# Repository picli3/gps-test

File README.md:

# gps-test

Plataforma de pruebas para GPS con **ESP32**, pantalla OLED, cargador, step-up y bloques auxiliares de interfaz.

## Propósito del proyecto
Este diseño parece orientado a validar o construir un equipo portátil de posicionamiento/visualización, integrando alimentación, procesamiento y despliegue de datos dentro de una sola solución modular.

## Qué incluye
- esquemáticos por bloques: GPS, ESP32, OLED, cargador, step-up y auxiliares
- PCB principal en KiCad
- base útil para experimentación con localización y dispositivos portátiles

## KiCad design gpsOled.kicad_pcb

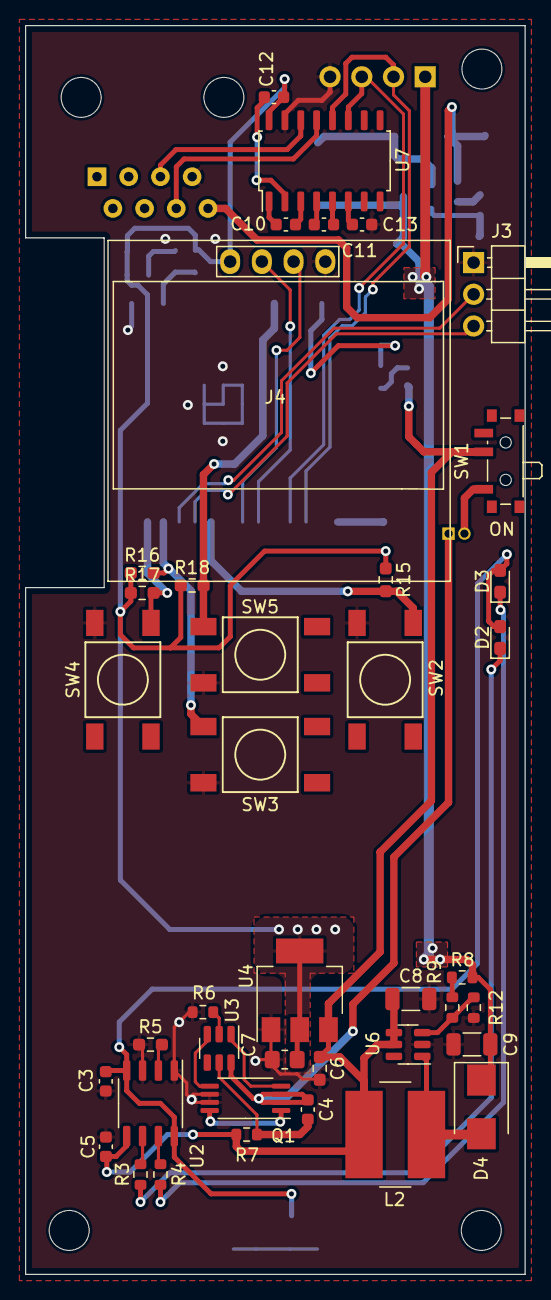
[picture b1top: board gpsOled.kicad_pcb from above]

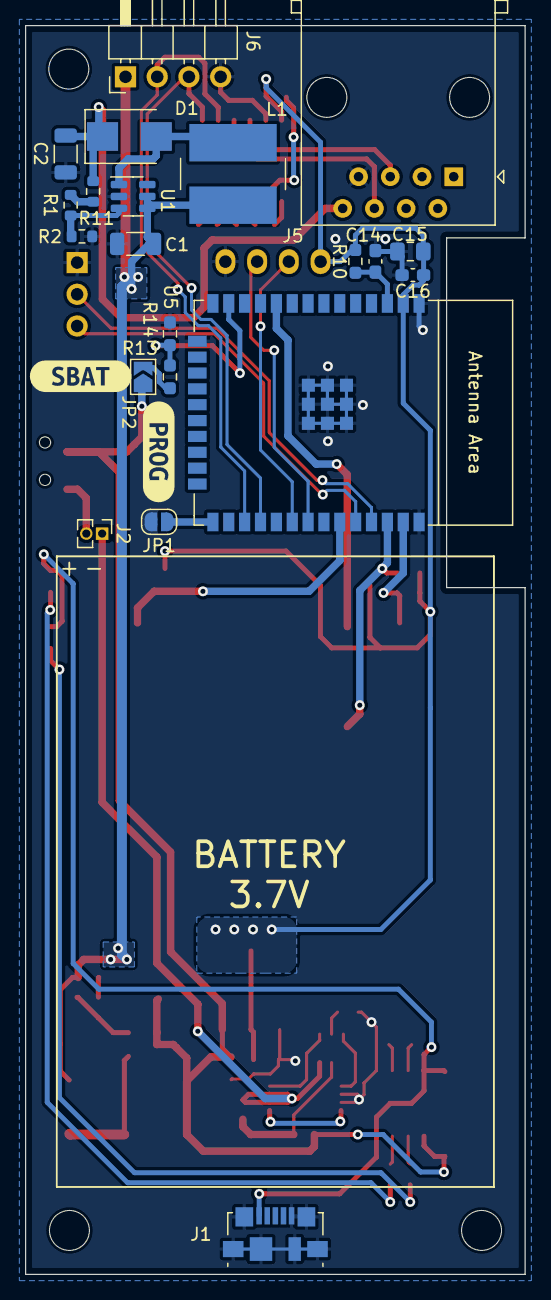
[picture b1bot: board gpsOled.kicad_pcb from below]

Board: 2 copper layers, 40.0 x 100.0 mm, 66 parts (23 on the bottom side), 46 nets.

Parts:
C1, C2, C8, C9: 22uF; C_1206_3216Metric
C3, C4: 0.1uF; C_0603_1608Metric
C5: 10uF; C_0603_1608Metric
C6: 0.1uF; R_0603_1608Metric_Pad0.98x0.95mm_HandSolder
C7: 10uF; R_0805_2012Metric_Pad1.20x1.40mm_HandSolder
C10: C; C_0603_1608Metric
C11, C12, C13: C_0603_1608Metric
C14, C16: 100nF; C_0603_1608Metric_Pad1.08x0.95mm_HandSolder
C15: 22uF; C_0805_2012Metric_Pad1.18x1.45mm_HandSolder
D1, D4: SS34; D_SMB
D2: B; LED_0603_1608Metric_Pad1.05x0.95mm_HandSolder
D3: R; LED_0603_1608Metric_Pad1.05x0.95mm_HandSolder
H1, H2: MountingHole; MountingHole_3.2mm_M3_DIN965
H3: MountingHole; MountingHole_3.2mm_M3
J1: USB_B_Micro; USB_Micro-B_Molex_47346-0001
J2: Conn_01x02; PinHeader_1x02_P1.27mm_Vertical
J3: Conn_01x03; PinHeader_1x03_P2.54mm_Horizontal
J4: SSD1306; 128x64OLED
J5: RJ45; RJ45_GEN_ZQP_Horizontal
J6: Conn_01x04; PinHeader_1x04_P2.54mm_Horizontal
JP1: Jumper_2_Open; SolderJumper-2_P1.3mm_Open_RoundedPad1.0x1.5mm
JP2: Jumper_2_Open; SolderJumper-2_P1.3mm_Open_TrianglePad1.0x1.5mm
L1, L2: 22uH; L_Bourns-SDE0805A_7x7.8mm
Q1: FS8205A; TSSOP-8_4.4x3mm_P0.65mm
R1: 22K; R_0603_1608Metric
R2, R12: 2.2k; R_0603_1608Metric
R3, R4, R6: 1k; R_0603_1608Metric
R5: 1.2k; R_0603_1608Metric_Pad0.98x0.95mm_HandSolder
R7: 100; R_0603_1608Metric
R8: 10K; R_0603_1608Metric
R9: 6.2K; R_0603_1608Metric
R10, R13, R14, R15, R16, R17, R18: 10k; R_0603_1608Metric_Pad0.98x0.95mm_HandSolder
R11: 20K; R_0603_1608Metric
SW1: on/off; SW_SPDT_PCM12
SW2, SW3, SW5: TL3301AF160QG
SW4: SW_Push; TL3301AF160QG
U1, U6: SDB628; SOT-23-6
U2: TP4056; SOP-8_3.9x4.9mm_P1.27mm
U3: DW01A; SOT-23-6
U4: AP1117-33; SOT-223-3_TabPin2
U5: ESP32-WROOM-E; ESP32-WROOM-32E
U7: MAX3232; SOIC-16_4.55x10.3mm_P1.27mm
kibuzzard-627F1822: G***; kibuzzard-627F1822
kibuzzard-629C15DA: G***; kibuzzard-629C15DA

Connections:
+3V3: C7.1, C12.1, C15.1, C16.1, J4.1, R10.1, R15.1, R16.1, R17.1, R18.1, U4.2 (VO), U5.2 (3V3), U7.16 (VCC)
+5V: C1.1, C9.1, D4.1 (K), J6.1, L1.1, R8.1, U1.4 (EN), U1.5 (IN)
+12V: C2.1, D1.1 (K), J5.8, R11.1
/ESP32/RST: C14.1, R10.2, U5.3 (EN/CHIP_PU)
/ESP32/SCL: J4.3, U5.31 (GPIO19)
/ESP32/SDA: J4.2, U5.30 (GPIO18)
/ESP32/UART_RX_0: J3.3, U5.34 (U0RXD/GPIO3)
/ESP32/UART_RX_2: J6.2, U5.27 (GPIO16), U7.12 (R1OUT)
/ESP32/UART_TX_0: J3.2, U5.35 (U0TXD/GPIO1)
/ESP32/UART_TX_2: J6.3, U5.28 (GPIO17), U7.11 (T1IN)
/RS232/RS232_TX: J5.5, U7.14 (T1OUT)
/RS232/RS323_RX: J5.6, U7.13 (R1IN)
/batt_status: JP2.2 (B), R13.1
/charger/BAT+: J2.2, SW1.1 (A)
/charger/BAT-: C4.2, J2.1, Q1.2 (D), Q1.3 (D), U3.6 (GND)
/charger/STEP-UP2/VIN: C5.1, C6.1, C8.1, JP2.1 (A), L2.1, R7.2, SW1.2 (B), U2.5 (BAT), U4.3 (VI), U6.4 (EN), U6.5 (IN)
/charger/VBUS: C3.1, D2.2 (A), D3.2 (A), J1.1 (VBUS), U2.4 (VCC), U2.8 (CE)
GND: C1.2, C2.2, C3.2, C5.2, C6.2, C7.2, C8.2, C9.2, C13.1, C14.2, C15.2, C16.2, J1.5 (GND), J1.6 (Shield), J3.1, J4.4, J5.7, J6.4, JP1.1 (A), Q1.6 (S), Q1.7 (S), R2.2, R5.1, R6.2, R12.2, R14.2, SW2.2, SW3.2, SW4.2, SW5.2, U1.2 (GND), U2.1 (TEMP), U2.3 (GND), U4.1 (GND), U5.1 (GND), U5.15 (GND), U5.38 (GND), U5.39 (GND_THERMAL), U6.2 (GND), U7.15 (GND)
unnamed: C4.1, R7.1, U3.5 (VCC)
unnamed: C10.1, U7.1 (C1+)
unnamed: C10.2, U7.3 (C1-)
unnamed: C11.1, U7.4 (C2+)
unnamed: C11.2, U7.5 (C2-)
unnamed: C12.2, U7.2 (VS+)
unnamed: C13.2, U7.6 (VS-)
unnamed: D1.2 (A), L1.2, U1.1 (SW)
unnamed: D2.1 (K), R3.2
unnamed: D3.1 (K), R4.2
unnamed: D4.2 (A), L2.2, U6.1 (SW)
unnamed: JP1.2 (B), U5.25 (GPIO0/BOOT/ADC2_CH1)
unnamed: Q1.1 (D), Q1.8 (D)
unnamed: Q1.4 (G), U3.1 (OD)
unnamed: Q1.5 (G), U3.3 (OC)
unnamed: R1.1, R11.2
unnamed: R1.2, R2.1, U1.3 (FB)
unnamed: R3.1, U2.6 (~STDBY)
unnamed: R4.1, U2.7 (~CHRG)
unnamed: R5.2, U2.2 (PROG)
unnamed: R6.1, U3.2 (CS)
unnamed: R8.2, R9.1
unnamed: R9.2, R12.1, U6.3 (FB)
unnamed: R18.2, SW5.1, U5.10 (DAC_1/ADC2_CH8/GPIO25)
unnamed: R13.2, R14.1, U5.13 (MTMS/GPIO14/ADC2_CH6)
unnamed: R15.2, SW2.1, U5.33 (GPIO21)
unnamed: R16.2, SW3.1, U5.36 (GPIO22)
unnamed: R17.2, SW4.1, U5.37 (GPIO23)

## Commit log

2022-04-10 version con circuito completo de pantalla SSD1306
2022-04-20 parcialmente terminada PCB falta verificar tamano de componentes
2022-05-02 cambiando solidos a step
2022-06-05 terminando, aun falta una ultima revision previa a la fabricacion
2022-06-05 generando gerbers
2026-04-29 Agrega README con descripción inicial del proyecto
2026-04-29 Mejora README con descripción específica del proyecto
